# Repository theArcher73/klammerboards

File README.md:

# Klammerboards Programmieradapter
 Boards für Testklammern
 
 attnodev2_prog - Programmieradapter mit Kontakten für Prog-Header und Sensor-Header

 attnodev2_prog_sml - Programmieradapter mit Kontakten für Prog-Header

 sensor - Adapter für den I<sub>2</sub>c-Anschluss

Disclaimer

The documentation of the Klammerboards Programmieradapter is distributed in the hope that it will be useful, but WITHOUT ANY WARRANTY; without even the implied warranty of MERCHANTABILITY or FITNESS FOR A PARTICULAR PURPOSE.

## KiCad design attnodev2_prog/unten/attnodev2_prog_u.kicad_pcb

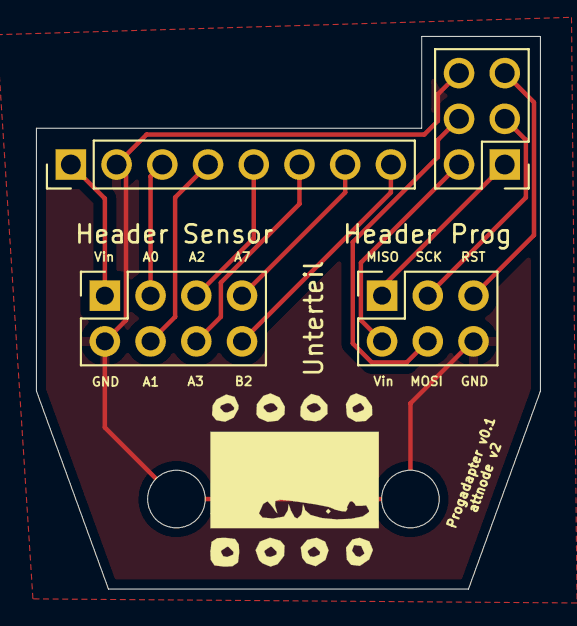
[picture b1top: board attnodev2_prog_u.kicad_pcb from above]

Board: 2 copper layers, 28.0 x 30.7 mm, 4 parts (0 on the bottom side), 13 nets.

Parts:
Header Prog: Connector:Conn_01x14_Female; PinSocket_2x03_P2.54mm_Vertical
Header Sensor: Connector:Conn_01x14_Female; PinSocket_2x04_P2.54mm_Vertical
J1: J1; PinHeader_1x08_P2.54mm_Vertical
PRG-Out1: PRG; PinHeader_2x03_P2.54mm_Vertical

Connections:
A0: Header Sensor.3, J1.3
A1: Header Sensor.4, J1.4
A2: Header Sensor.5, J1.5
A3: Header Sensor.6, J1.6
A7: Header Sensor.7, J1.7
B2: Header Sensor.8, J1.8
GND: Header Prog.6, Header Sensor.2, J1.2, PRG-Out1.6
MISO: Header Prog.1, PRG-Out1.1
MOSI: Header Prog.4, PRG-Out1.4
PRG_Vin: Header Prog.2, PRG-Out1.2
RST: Header Prog.5, PRG-Out1.5
SCK: Header Prog.3, PRG-Out1.3
Vin: Header Sensor.1, J1.1

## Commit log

2021-02-09 initial load
2021-02-19 added 3d
